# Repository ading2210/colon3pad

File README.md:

# colon3pad

This is a custom designed macro pad, created for the the [Hackpad](https://hackpad.hackclub.com/) event. It has 16 keys and a built in OLED display.

## Inspiration / Challenges:

I designed this so I could get more practice with designing PCBs in KiCad. The fact that I'm [getting this hardware for free](https://hackpad.hackclub.com) also gave me an excuse to work on it. 

A challenge that I had was that I had to redo parts of the design several times. For example, I had finished the PCB when I realized that all the switches needed to be rotated 180°, so that forced me to reroute everything. Also, information on the PCB footprints and dimensions needed for the Choc V2 switches is somewhat scarce, so a ton of research was required. 

## BOM:
For PCB:
- 1x Seeed Studio XIAO RP2040 
- 1x SSD1306 128x32 OLED 
- 16x Kailh Choc V2 switches
- 16x SK6812-E reverse mount NeoPixel LEDs
- 16x 1N4148 diodes 

For Case:
- Case is 3D printed with PLA
- 4x M3x12mm screws
- 4x M3 hex nuts
- 4x M3x5mx4mm heatset inserts
- 15x 1u low profile key caps ([compatibility list](https://docs.google.com/spreadsheets/d/1ylYmEZ1jNiPuHWl6rjiI3xzooOwUTS33BZfYSW-n7Ok/edit?gid=0#gid=0))
- 1x 2u low profile key cap

## License:
This project is licensed under the GNU GPL v3. 
```
ading2210/colon3pad - A custom macro pad
Copyright (C) 2025 ading2210

This program is free software: you can redistribute it and/or modify
it under the terms of the GNU General Public License as published by
the Free Software Foundation, either version 3 of the License, or
(at your option) any later version.

This program is distributed in the hope that it will be useful,
but WITHOUT ANY WARRANTY; without even the implied warranty of
MERCHANTABILITY or FITNESS FOR A PARTICULAR PURPOSE.  See the
GNU General Public License for more details.

You should have received a copy of the GNU General Public License
along with this program.  If not, see <https://www.gnu.org/licenses/>.
```

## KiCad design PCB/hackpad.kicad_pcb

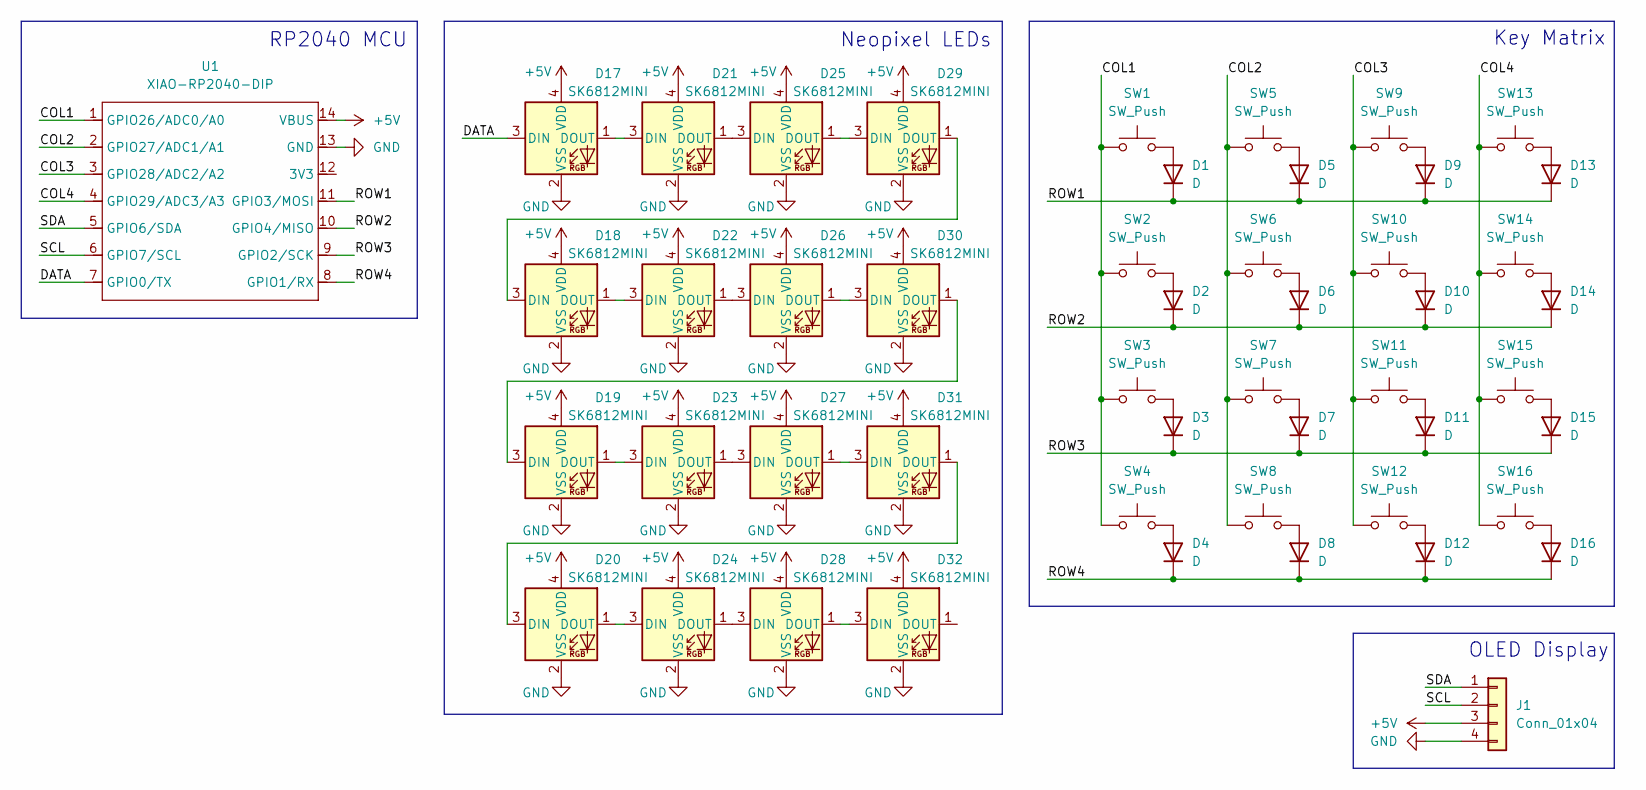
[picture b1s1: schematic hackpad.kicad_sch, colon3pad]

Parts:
D1, D2, D3, D4, D5, D6, D7, D8, D9, D10, D11, D12, D13, D14, D15, D16: D; D_DO-35_SOD27_P7.62mm_Horizontal
D17, D18, D19, D20, D21, D22, D23, D24, D25, D26, D27, D28, D29, D30, D31, D32: SK6812MINI; SK6812-MINI-E
J1: Conn_01x04; SSD1306-0.91-OLED-4pin-128x32
SW1, SW2, SW3, SW4, SW5, SW6, SW7, SW8, SW9, SW10, SW11, SW12, SW13, SW14, SW15, SW16: SW_Push; SW_Kailh_Choc_V2_1.00u
U1: XIAO-RP2040-DIP; MOUDLE14P-XIAO-DIP-SMD

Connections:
+5V: D17.4 (VDD), D18.4 (VDD), D19.4 (VDD), D20.4 (VDD), D21.4 (VDD), D22.4 (VDD), D23.4 (VDD), D24.4 (VDD), D25.4 (VDD), D26.4 (VDD), D27.4 (VDD), D28.4 (VDD), D29.4 (VDD), D30.4 (VDD), D31.4 (VDD), D32.4 (VDD), J1.3, U1.14 (VBUS)
/COL1: SW1.1, SW2.1, SW3.1, SW4.1, U1.1 (GPIO26/ADC0/A0)
/COL2: SW5.1, SW6.1, SW7.1, SW8.1, U1.2 (GPIO27/ADC1/A1)
/COL3: SW9.1, SW10.1, SW11.1, SW12.1, U1.3 (GPIO28/ADC2/A2)
/COL4: SW13.1, SW14.1, SW15.1, SW16.1, U1.4 (GPIO29/ADC3/A3)
/DATA: D17.3 (DIN), U1.7 (GPIO0/TX)
/ROW1: D1.1 (K), D5.1 (K), D9.1 (K), D13.1 (K), U1.11 (GPIO3/MOSI)
/ROW2: D2.1 (K), D6.1 (K), D10.1 (K), D14.1 (K), U1.10 (GPIO4/MISO)
/ROW3: D3.1 (K), D7.1 (K), D11.1 (K), D15.1 (K), U1.9 (GPIO2/SCK)
/ROW4: D4.1 (K), D8.1 (K), D12.1 (K), D16.1 (K), U1.8 (GPIO1/RX)
/SCL: J1.2, U1.6 (GPIO7/SCL)
/SDA: J1.1, U1.5 (GPIO6/SDA)
GND: D17.2 (VSS), D18.2 (VSS), D19.2 (VSS), D20.2 (VSS), D21.2 (VSS), D22.2 (VSS), D23.2 (VSS), D24.2 (VSS), D25.2 (VSS), D26.2 (VSS), D27.2 (VSS), D28.2 (VSS), D29.2 (VSS), D30.2 (VSS), D31.2 (VSS), D32.2 (VSS), J1.4, U1.13 (GND)
unnamed: D1.2 (A), SW1.2
unnamed: D2.2 (A), SW2.2
unnamed: D3.2 (A), SW3.2
unnamed: D4.2 (A), SW4.2
unnamed: D5.2 (A), SW5.2
unnamed: D6.2 (A), SW6.2
unnamed: D7.2 (A), SW7.2
unnamed: D8.2 (A), SW8.2
unnamed: D9.2 (A), SW9.2
unnamed: D10.2 (A), SW10.2
unnamed: D11.2 (A), SW11.2
unnamed: D12.2 (A), SW12.2
unnamed: D13.2 (A), SW13.2
unnamed: D14.2 (A), SW14.2
unnamed: D15.2 (A), SW15.2
unnamed: D16.2 (A), SW16.2
unnamed: D17.1 (DOUT), D21.3 (DIN)
unnamed: D18.3 (DIN), D29.1 (DOUT)
unnamed: D18.1 (DOUT), D22.3 (DIN)
unnamed: D19.3 (DIN), D30.1 (DOUT)
unnamed: D19.1 (DOUT), D23.3 (DIN)
unnamed: D20.3 (DIN), D31.1 (DOUT)
unnamed: D20.1 (DOUT), D24.3 (DIN)
unnamed: D21.1 (DOUT), D25.3 (DIN)
unnamed: D22.1 (DOUT), D26.3 (DIN)
unnamed: D23.1 (DOUT), D27.3 (DIN)
unnamed: D24.1 (DOUT), D28.3 (DIN)
unnamed: D25.1 (DOUT), D29.3 (DIN)
unnamed: D26.1 (DOUT), D30.3 (DIN)
unnamed: D27.1 (DOUT), D31.3 (DIN)
unnamed: D28.1 (DOUT), D32.3 (DIN)

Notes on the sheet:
OLED Display
Neopixel LEDs
Key Matrix
RP2040 MCU

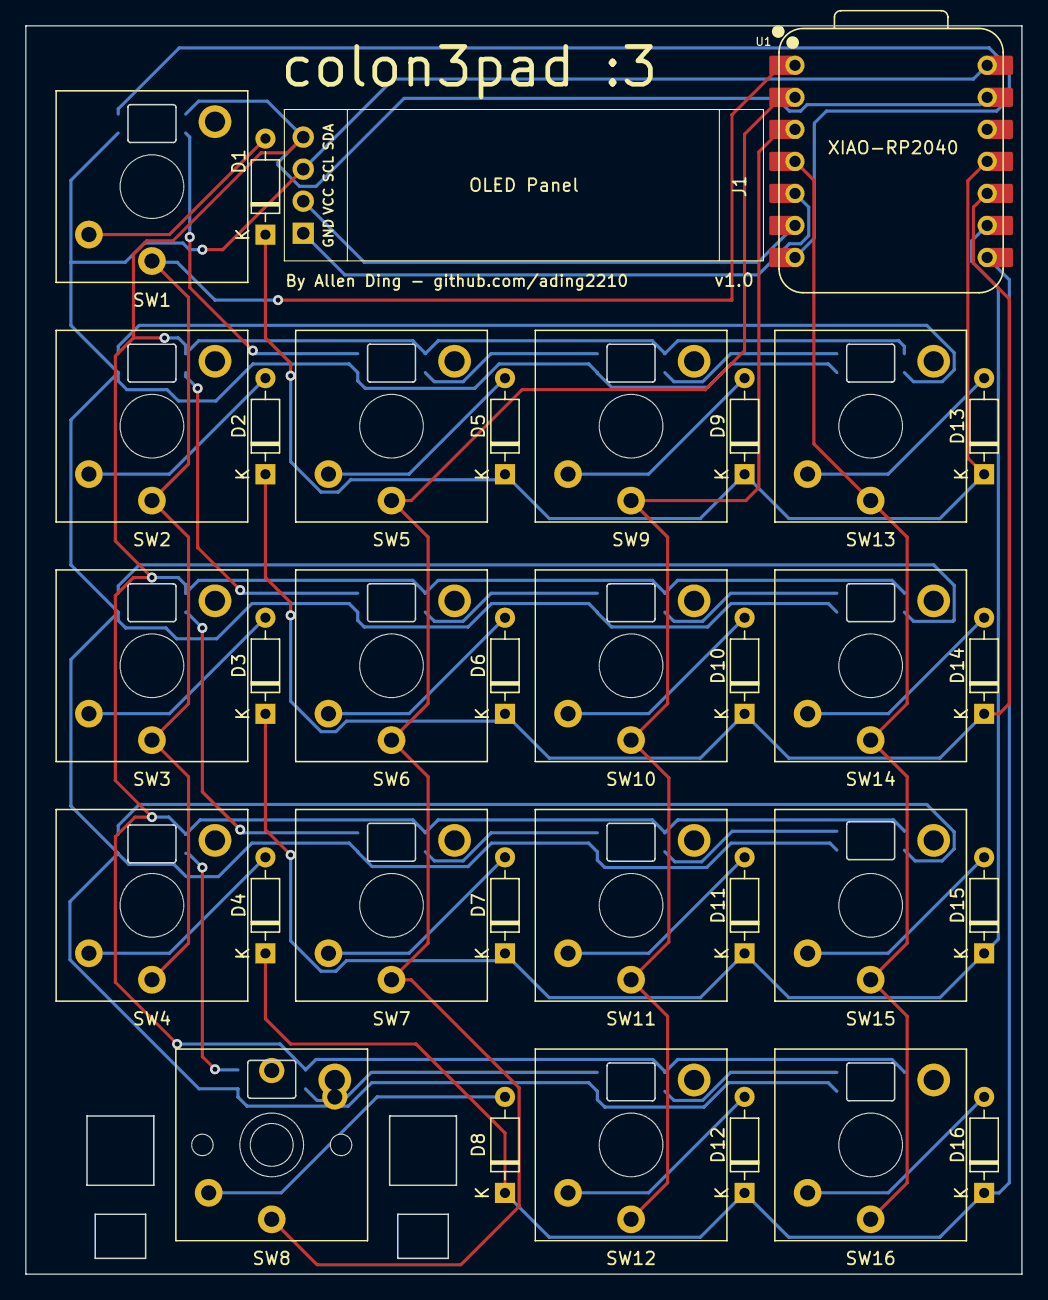
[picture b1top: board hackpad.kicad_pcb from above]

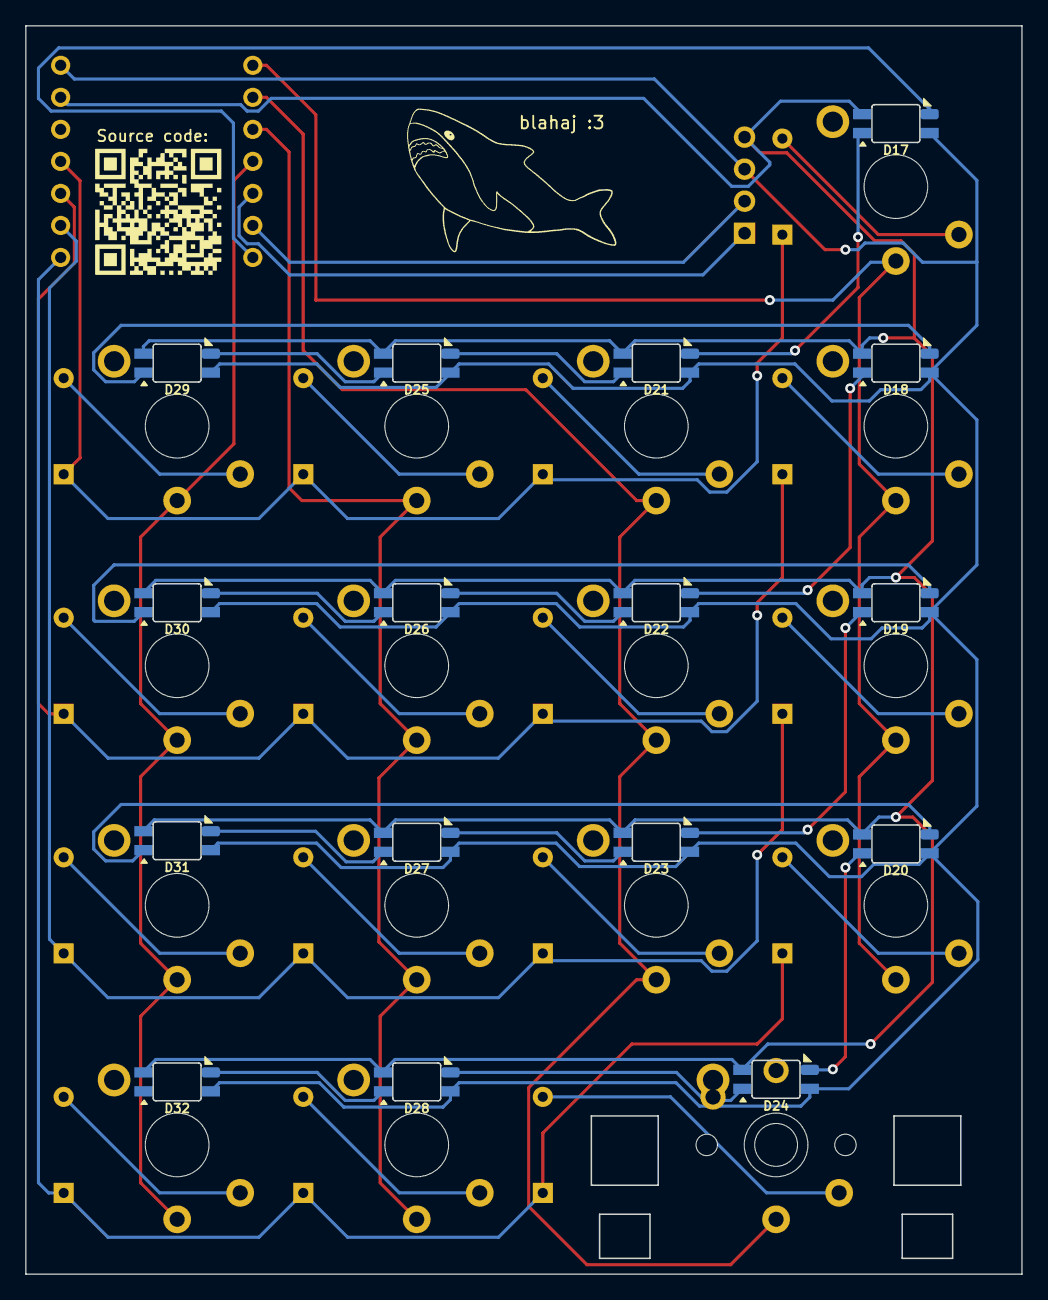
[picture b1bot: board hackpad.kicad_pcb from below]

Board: 2 copper layers, 79.0 x 99.0 mm, 51 parts (16 on the bottom side), 44 nets.

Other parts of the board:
2u: Choc-2u-solder

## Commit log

2025-02-17 add keys, oled, neopixels to schematic
2025-02-17 add footprint submodules, first version of the pcb
2025-02-17 add branding to pcb
2025-02-17 add 3d models to pcb
2025-02-17 rotate all key switches and redo routing
2025-02-17 move all pcb stuff into subdirectory
2025-02-17 add fusion360 cad files
2025-02-18 finalize pcb traces and silkscreen text
2025-02-19 add cutouts for key stabilizer
2025-02-19 add draft for firmware
2025-02-19 add license, readme, and bom
2025-02-20 add images to readme
2025-02-20 update pcb with new footprint for stabilizer
2025-02-20 update case cad files
2025-02-21 export gerber files
2025-03-24 add initial kicad files for hackboard
2025-03-24 move kicad libraries to third_party dir, update to kicad 9.0
2025-03-24 Revert "add initial kicad files for hackboard"
    This reverts commit 026ab9f43395aebb26b94a7c593d4d996977a634.
